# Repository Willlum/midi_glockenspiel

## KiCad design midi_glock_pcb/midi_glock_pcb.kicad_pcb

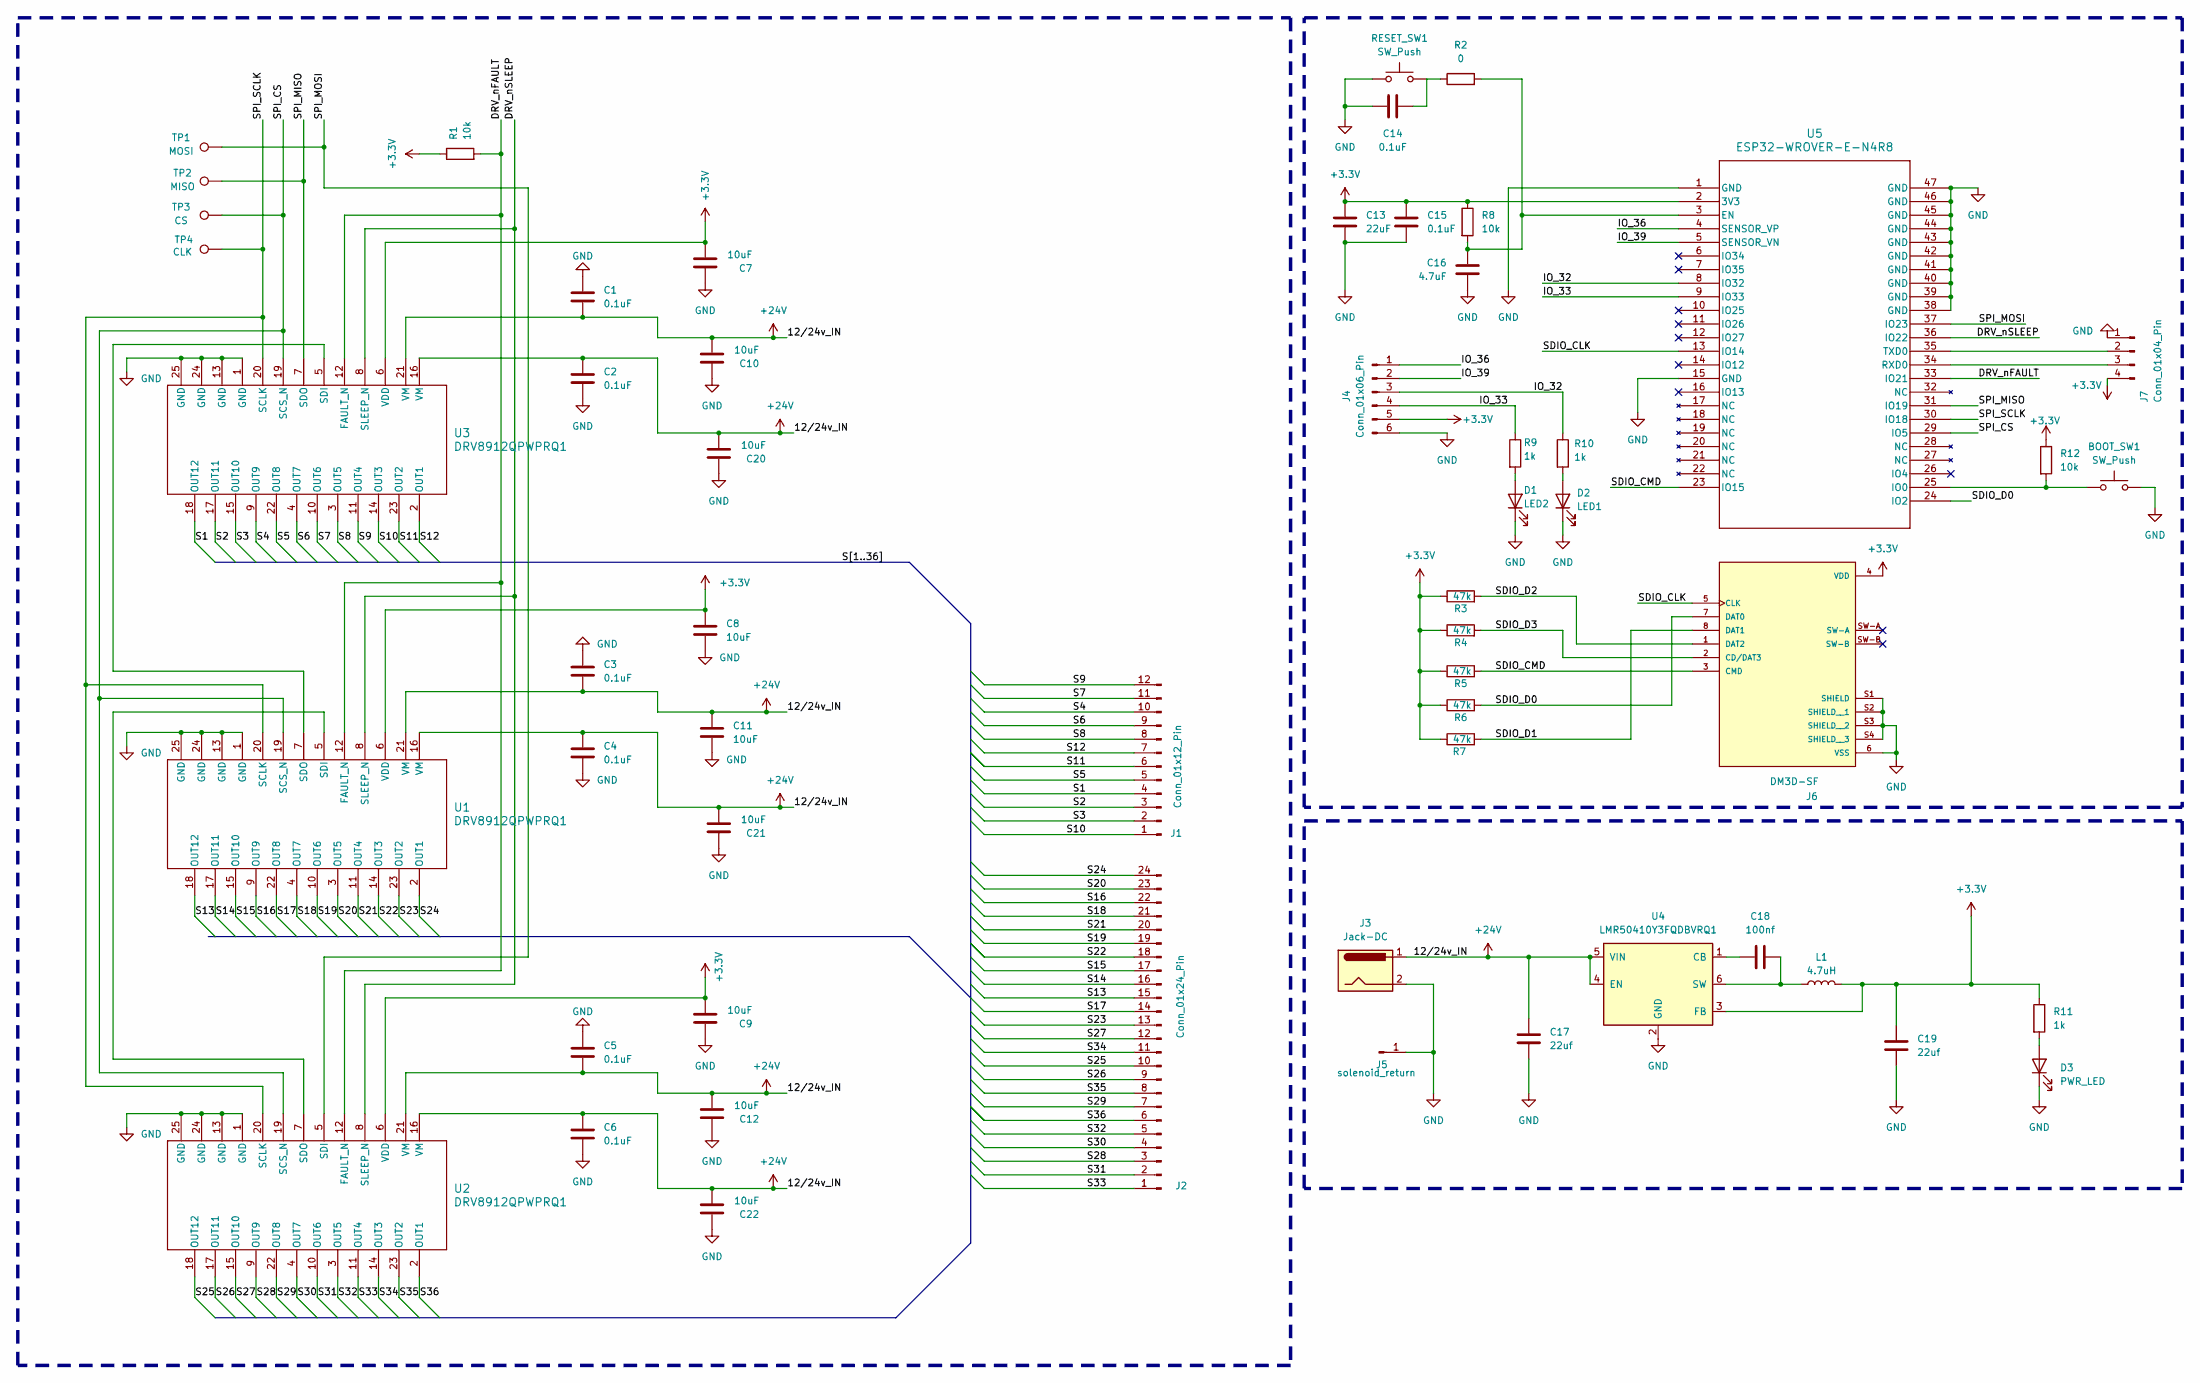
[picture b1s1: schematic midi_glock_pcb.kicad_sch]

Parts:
BOOT_SW1: SW_Push; SW_SPST_Omron_B3FS-100xP
C1, C2, C3, C4, C5, C6, C14, C15: 0.1uF; C_0603_1608Metric_Pad1.08x0.95mm_HandSolder
C7, C8, C9: 10uF; C_0805_2012Metric_Pad1.18x1.45mm_HandSolder
C10, C11, C12, C20, C21, C22: 10uF; C_1206_3216Metric
C13: 22uF; C_1210_3225Metric
C16: 4.7uF; C_0805_2012Metric_Pad1.18x1.45mm_HandSolder
C17, C19: 22uf; C_1210_3225Metric
C18: 100nf; C_0603_1608Metric_Pad1.08x0.95mm_HandSolder
D1: LED2; LED_0805_2012Metric_Pad1.15x1.40mm_HandSolder
D2: LED1; LED_0805_2012Metric_Pad1.15x1.40mm_HandSolder
D3: PWR_LED; LED_0805_2012Metric_Pad1.15x1.40mm_HandSolder
J1: Conn_01x12_Pin; PHOENIX_1989845
J2: Conn_01x24_Pin; PHOENIX_1990232
J3: Jack-DC; BarrelJack_Horizontal
J4: Conn_01x06_Pin; PinHeader_2x03_P2.54mm_Vertical
J5: solenoid_return; Pin_D1.3mm_L11.0mm_LooseFit
J6: DM3D-SF; HRS_DM3D-SF; PARTREV 2017.1
J7: Conn_01x04_Pin; PinHeader_1x04_P2.54mm_Vertical
L1: 4.7uH; IND_SRP4020TA-4R7M
R1, R8, R12: 10k; R_0603_1608Metric_Pad0.98x0.95mm_HandSolder
R2: 0; R_0603_1608Metric_Pad0.98x0.95mm_HandSolder
R3, R4, R5, R6, R7: 47k; R_0603_1608Metric_Pad0.98x0.95mm_HandSolder
R9, R10, R11: 1k; R_0603_1608Metric_Pad0.98x0.95mm_HandSolder
RESET_SW1: SW_Push; SW_SPST_Omron_B3FS-100xP
TP1: MOSI; TestPoint_Pad_D1.0mm
TP2: MISO; TestPoint_Pad_D1.0mm
TP3: CS; TestPoint_Pad_D1.0mm
TP4: CLK; TestPoint_Pad_D1.0mm
U1, U2, U3: DRV8912QPWPRQ1; PWP0024N_N
U4: LMR50410Y3FQDBVRQ1; SOT-23-6
U5: ESP32-WROVER-E-N4R8; ESP32­WROVER­E&slash_ESP32­WROVER­IE_EXP

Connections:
+3.3V: C7.2, C8.1, C9.2, C13.1, C15.1, C19.1, J4.5, J6.4 (VDD), J7.4, L1.2, R1.1, R3.1, R4.1, R5.1, R6.1, R7.1, R8.1, R11.1, R12.1, U1.6 (VDD), U2.6 (VDD), U3.6 (VDD), U4.3 (FB), U5.2 (3V3)
+24V: C1.2, C2.2, C3.2, C4.2, C5.2, C6.2, C10.2, C11.2, C12.2, C17.1, C20.2, C21.2, C22.2, J3.1, U1.16 (VM), U1.21 (VM), U2.16 (VM), U2.21 (VM), U3.16 (VM), U3.21 (VM), U4.4 (EN), U4.5 (VIN)
/DRV_nFAULT: R1.2, U1.12 (FAULT_N), U2.12 (FAULT_N), U3.12 (FAULT_N), U5.33 (IO21)
/DRV_nSLEEP: U1.8 (SLEEP_N), U2.8 (SLEEP_N), U3.8 (SLEEP_N), U5.36 (IO22)
/IO_32: J4.3, R10.1, U5.8 (IO32)
/IO_33: J4.4, R9.1, U5.9 (IO33)
/IO_36: J4.1, U5.4 (SENSOR_VP)
/IO_39: J4.2, U5.5 (SENSOR_VN)
/S1: J1.4, U3.18 (OUT12)
/S2: J1.3, U3.17 (OUT11)
/S3: J1.2, U3.15 (OUT10)
/S4: J1.10, U3.9 (OUT9)
/S5: J1.5, U3.22 (OUT8)
/S6: J1.9, U3.4 (OUT7)
/S7: J1.11, U3.10 (OUT6)
/S8: J1.8, U3.3 (OUT5)
/S9: J1.12, U3.11 (OUT4)
/S10: J1.1, U3.14 (OUT3)
/S11: J1.6, U3.23 (OUT2)
/S12: J1.7, U3.2 (OUT1)
/S13: J2.15, U1.18 (OUT12)
/S14: J2.16, U1.17 (OUT11)
/S15: J2.17, U1.15 (OUT10)
/S16: J2.22, U1.9 (OUT9)
/S17: J2.14, U1.22 (OUT8)
/S18: J2.21, U1.4 (OUT7)
/S19: J2.19, U1.10 (OUT6)
/S20: J2.23, U1.3 (OUT5)
/S21: J2.20, U1.11 (OUT4)
/S22: J2.18, U1.14 (OUT3)
/S23: J2.13, U1.23 (OUT2)
/S24: J2.24, U1.2 (OUT1)
/S25: J2.10, U2.18 (OUT12)
/S26: J2.9, U2.17 (OUT11)
/S27: J2.12, U2.15 (OUT10)
/S28: J2.3, U2.9 (OUT9)
/S29: J2.7, U2.22 (OUT8)
/S30: J2.4, U2.4 (OUT7)
/S31: J2.2, U2.10 (OUT6)
/S32: J2.5, U2.3 (OUT5)
/S33: J2.1, U2.11 (OUT4)
/S34: J2.11, U2.14 (OUT3)
/S35: J2.8, U2.23 (OUT2)
/S36: J2.6, U2.2 (OUT1)
/SDIO_CLK: J6.5 (CLK), U5.13 (IO14)
/SDIO_CMD: J6.3 (CMD), R5.2, U5.23 (IO15)
/SDIO_D0: J6.7 (DAT0), R6.2, U5.24 (IO2)
/SDIO_D1: J6.8 (DAT1), R7.2
/SDIO_D2: J6.1 (DAT2), R3.2
/SDIO_D3: J6.2 (CD/DAT3), R4.2
/SPI_CS: TP3.1 (1_1), U1.19 (SCS_N), U2.19 (SCS_N), U3.19 (SCS_N), U5.29 (IO5)
/SPI_MISO: TP2.1 (1_1), U3.7 (SDO), U5.31 (IO19)
/SPI_MOSI: TP1.1 (1_1), U2.5 (SDI), U5.37 (IO23)
/SPI_SCLK: TP4.1 (1_1), U1.20 (SCLK), U2.20 (SCLK), U3.20 (SCLK), U5.30 (IO18)
GND: BOOT_SW1.1, C1.1, C2.1, C3.1, C4.1, C5.1, C6.1, C7.1, C8.2, C9.1, C10.1, C11.1, C12.1, C13.2, C14.1, C15.2, C16.2, C17.2, C19.2, C20.1, C21.1, C22.1, D1.1 (K), D2.1 (K), D3.1 (K), J3.2, J4.6, J5.1 (Pin_1_1), J6.6 (VSS), J6.S1 (SHIELD), J6.S2 (SHIELD__1), J6.S3 (SHIELD__2), J6.S4 (SHIELD__3), J7.1, RESET_SW1.1, U1.1 (GND), U1.13 (GND), U1.24 (GND), U1.25 (GND), U2.1 (GND), U2.13 (GND), U2.24 (GND), U2.25 (GND), U3.1 (GND), U3.13 (GND), U3.24 (GND), U3.25 (GND), U4.2 (GND), U5.1 (GND), U5.15 (GND), U5.38 (GND), U5.39 (GND), U5.40 (GND), U5.41 (GND), U5.42 (GND), U5.43 (GND), U5.44 (GND), U5.45 (GND), U5.46 (GND), U5.47 (GND)
unnamed: C14.2, R2.1, RESET_SW1.2
unnamed: D1.2 (A), R9.2
unnamed: D2.2 (A), R10.2
unnamed: D3.2 (A), R11.2
unnamed: J7.2, U5.35 (TXD0)
unnamed: J7.3, U5.34 (RXD0)
unnamed: U1.5 (SDI), U2.7 (SDO)
unnamed: U1.7 (SDO), U3.5 (SDI)
unnamed: C18.1, U4.1 (CB)
unnamed: C18.2, L1.1, U4.6 (SW)
unnamed: C16.1, R2.2, R8.2, U5.3 (EN)
unnamed: BOOT_SW1.2, R12.2, U5.25 (IO0)

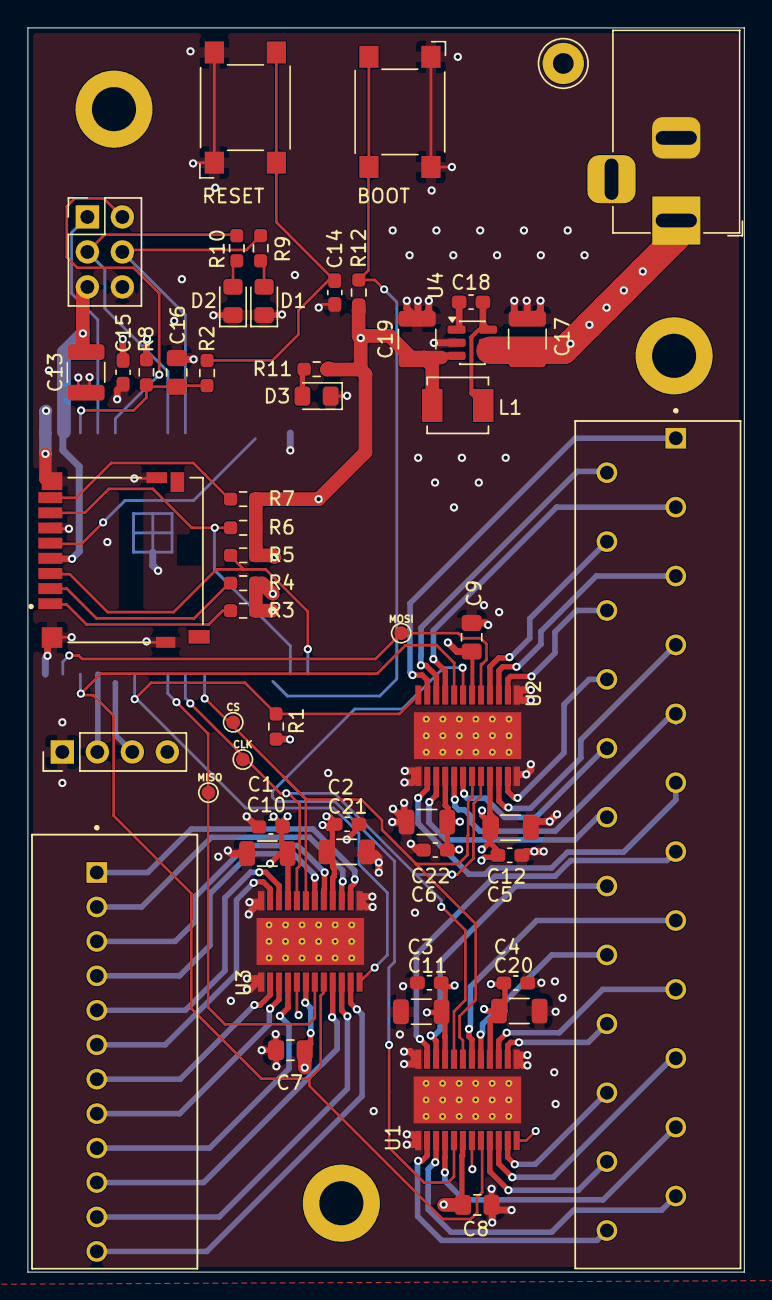
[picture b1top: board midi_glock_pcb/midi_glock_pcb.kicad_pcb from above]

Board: 4 copper layers, 52.0 x 90.3 mm, 56 parts (1 on the bottom side), 67 nets.

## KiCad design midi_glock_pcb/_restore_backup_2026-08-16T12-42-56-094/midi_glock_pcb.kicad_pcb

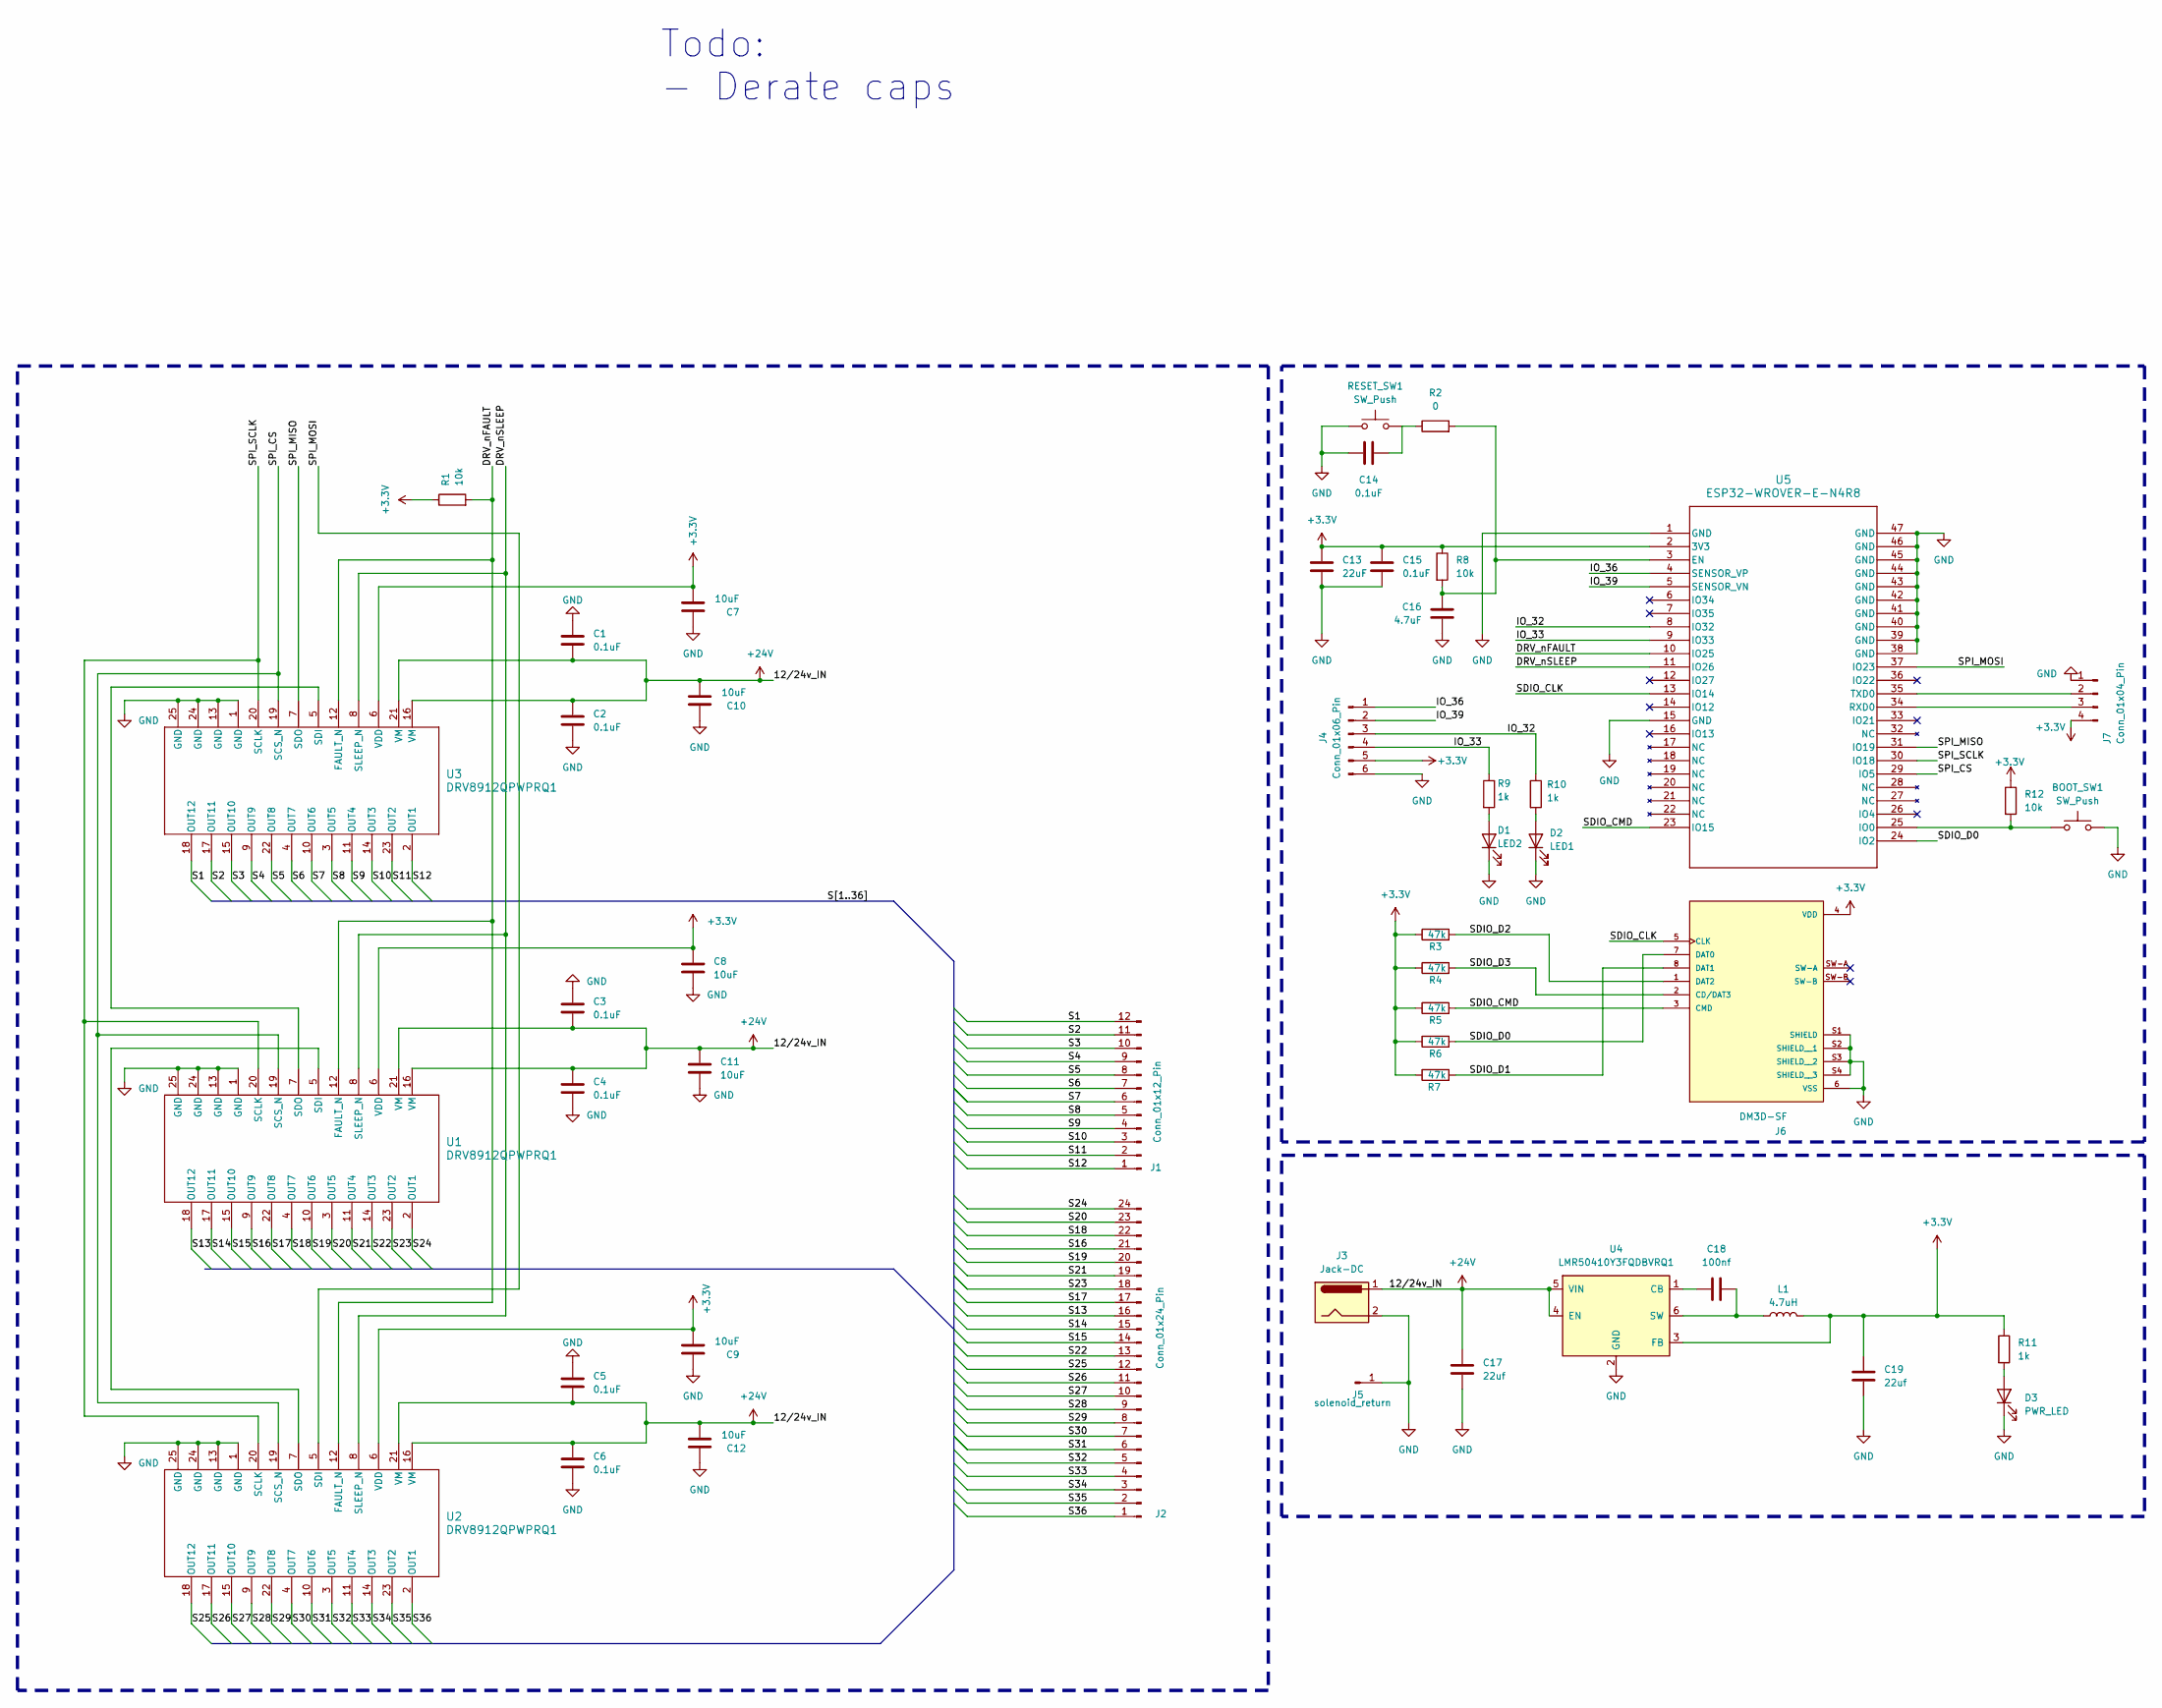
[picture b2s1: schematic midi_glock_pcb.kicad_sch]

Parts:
BOOT_SW1: SW_Push; SW_SPST_Omron_B3FS-100xP
C1, C2, C3, C4, C5, C6, C14, C15: 0.1uF; C_0805_2012Metric_Pad1.18x1.45mm_HandSolder
C7, C8, C9, C10, C11, C12: 10uF; C_0805_2012Metric_Pad1.18x1.45mm_HandSolder
C13: 22uF; C_0805_2012Metric_Pad1.18x1.45mm_HandSolder
C16: 4.7uF; C_0805_2012Metric_Pad1.18x1.45mm_HandSolder
C17, C19: 22uf; C_0805_2012Metric_Pad1.18x1.45mm_HandSolder
C18: 100nf; C_0805_2012Metric_Pad1.18x1.45mm_HandSolder
D1: LED2; LED_0805_2012Metric_Pad1.15x1.40mm_HandSolder
D2: LED1; LED_0805_2012Metric_Pad1.15x1.40mm_HandSolder
D3: PWR_LED; LED_0805_2012Metric_Pad1.15x1.40mm_HandSolder
J1: Conn_01x12_Pin; PHOENIX_1989845
J2: Conn_01x24_Pin; PHOENIX_1990232
J3: Jack-DC; BarrelJack_Horizontal
J4: Conn_01x06_Pin; PinHeader_2x03_P2.54mm_Vertical
J5: solenoid_return; Pin_D1.3mm_L11.0mm_LooseFit
J6: DM3D-SF; HRS_DM3D-SF; PARTREV 2017.1
J7: Conn_01x04_Pin; PinHeader_1x04_P2.54mm_Vertical
L1: 4.7uH; IND_SRP4020TA-4R7M
R1, R8, R12: 10k; R_0805_2012Metric_Pad1.20x1.40mm_HandSolder
R2: 0; R_0805_2012Metric_Pad1.20x1.40mm_HandSolder
R3, R4, R5, R6, R7: 47k; R_0805_2012Metric_Pad1.20x1.40mm_HandSolder
R9, R10, R11: 1k; R_0805_2012Metric_Pad1.20x1.40mm_HandSolder
RESET_SW1: SW_Push; SW_SPST_Omron_B3FS-100xP
U1, U2, U3: DRV8912QPWPRQ1; PWP0024N_N
U4: LMR50410Y3FQDBVRQ1; SOT-23-6
U5: ESP32-WROVER-E-N4R8; ESP32­WROVER­E&slash_ESP32­WROVER­IE_EXP

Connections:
+3.3V: C7.2, C8.1, C9.2, C13.1, C15.1, C19.1, J4.5, J6.4 (VDD), J7.4, L1.2, R1.1, R3.1, R4.1, R5.1, R6.1, R7.1, R8.1, R11.1, R12.1, U1.6 (VDD), U2.6 (VDD), U3.6 (VDD), U4.3 (FB), U5.2 (3V3)
+24V: C1.2, C2.2, C3.2, C4.2, C5.2, C6.2, C10.2, C11.2, C12.2, C17.1, J3.1, U1.16 (VM), U1.21 (VM), U2.16 (VM), U2.21 (VM), U3.16 (VM), U3.21 (VM), U4.4 (EN), U4.5 (VIN)
/DRV_nFAULT: R1.2, U1.12 (FAULT_N), U2.12 (FAULT_N), U3.12 (FAULT_N), U5.10 (IO25)
/DRV_nSLEEP: U1.8 (SLEEP_N), U2.8 (SLEEP_N), U3.8 (SLEEP_N), U5.11 (IO26)
/IO_32: J4.3, R10.1, U5.8 (IO32)
/IO_33: J4.4, R9.1, U5.9 (IO33)
/IO_36: J4.1, U5.4 (SENSOR_VP)
/IO_39: J4.2, U5.5 (SENSOR_VN)
/S1: J1.12, U3.18 (OUT12)
/S2: J1.11, U3.17 (OUT11)
/S3: J1.10, U3.15 (OUT10)
/S4: J1.9, U3.9 (OUT9)
/S5: J1.8, U3.22 (OUT8)
/S6: J1.7, U3.4 (OUT7)
/S7: J1.6, U3.10 (OUT6)
/S8: J1.5, U3.3 (OUT5)
/S9: J1.4, U3.11 (OUT4)
/S10: J1.3, U3.14 (OUT3)
/S11: J1.2, U3.23 (OUT2)
/S12: J1.1, U3.2 (OUT1)
/S13: J2.16, U1.18 (OUT12)
/S14: J2.15, U1.17 (OUT11)
/S15: J2.14, U1.15 (OUT10)
/S16: J2.21, U1.9 (OUT9)
/S17: J2.17, U1.22 (OUT8)
/S18: J2.22, U1.4 (OUT7)
/S19: J2.20, U1.10 (OUT6)
/S20: J2.23, U1.3 (OUT5)
/S21: J2.19, U1.11 (OUT4)
/S22: J2.13, U1.14 (OUT3)
/S23: J2.18, U1.23 (OUT2)
/S24: J2.24, U1.2 (OUT1)
/S25: J2.12, U2.18 (OUT12)
/S26: J2.11, U2.17 (OUT11)
/S27: J2.10, U2.15 (OUT10)
/S28: J2.9, U2.9 (OUT9)
/S29: J2.8, U2.22 (OUT8)
/S30: J2.7, U2.4 (OUT7)
/S31: J2.6, U2.10 (OUT6)
/S32: J2.5, U2.3 (OUT5)
/S33: J2.4, U2.11 (OUT4)
/S34: J2.3, U2.14 (OUT3)
/S35: J2.2, U2.23 (OUT2)
/S36: J2.1, U2.2 (OUT1)
/SDIO_CLK: J6.5 (CLK), U5.13 (IO14)
/SDIO_CMD: J6.3 (CMD), R5.2, U5.23 (IO15)
/SDIO_D0: J6.7 (DAT0), R6.2, U5.24 (IO2)
/SDIO_D1: J6.8 (DAT1), R7.2
/SDIO_D2: J6.1 (DAT2), R3.2
/SDIO_D3: J6.2 (CD/DAT3), R4.2
/SPI_CS: U1.19 (SCS_N), U2.19 (SCS_N), U3.19 (SCS_N), U5.29 (IO5)
/SPI_MISO: U3.7 (SDO), U5.31 (IO19)
/SPI_MOSI: U2.5 (SDI), U5.37 (IO23)
/SPI_SCLK: U1.20 (SCLK), U2.20 (SCLK), U3.20 (SCLK), U5.30 (IO18)
GND: BOOT_SW1.1, C1.1, C2.1, C3.1, C4.1, C5.1, C6.1, C7.1, C8.2, C9.1, C10.1, C11.1, C12.1, C13.2, C14.1, C15.2, C16.2, C17.2, C19.2, D1.1 (K), D2.1 (K), D3.1 (K), J3.2, J4.6, J5.1 (Pin_1_1), J6.6 (VSS), J6.S1 (SHIELD), J6.S2 (SHIELD__1), J6.S3 (SHIELD__2), J6.S4 (SHIELD__3), J7.1, RESET_SW1.1, U1.1 (GND), U1.13 (GND), U1.24 (GND), U1.25 (GND), U2.1 (GND), U2.13 (GND), U2.24 (GND), U2.25 (GND), U3.1 (GND), U3.13 (GND), U3.24 (GND), U3.25 (GND), U4.2 (GND), U5.1 (GND), U5.15 (GND), U5.38 (GND), U5.39 (GND), U5.40 (GND), U5.41 (GND), U5.42 (GND), U5.43 (GND), U5.44 (GND), U5.45 (GND), U5.46 (GND), U5.47 (GND)
unnamed: C14.2, R2.1, RESET_SW1.2
unnamed: D1.2 (A), R9.2
unnamed: D2.2 (A), R10.2
unnamed: D3.2 (A), R11.2
unnamed: J7.2, U5.35 (TXD0)
unnamed: J7.3, U5.34 (RXD0)
unnamed: U1.5 (SDI), U2.7 (SDO)
unnamed: U1.7 (SDO), U3.5 (SDI)
unnamed: C18.1, U4.1 (CB)
unnamed: C18.2, L1.1, U4.6 (SW)
unnamed: C16.1, R2.2, R8.2, U5.3 (EN)
unnamed: BOOT_SW1.2, R12.2, U5.25 (IO0)

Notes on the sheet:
Todo: - Derate caps

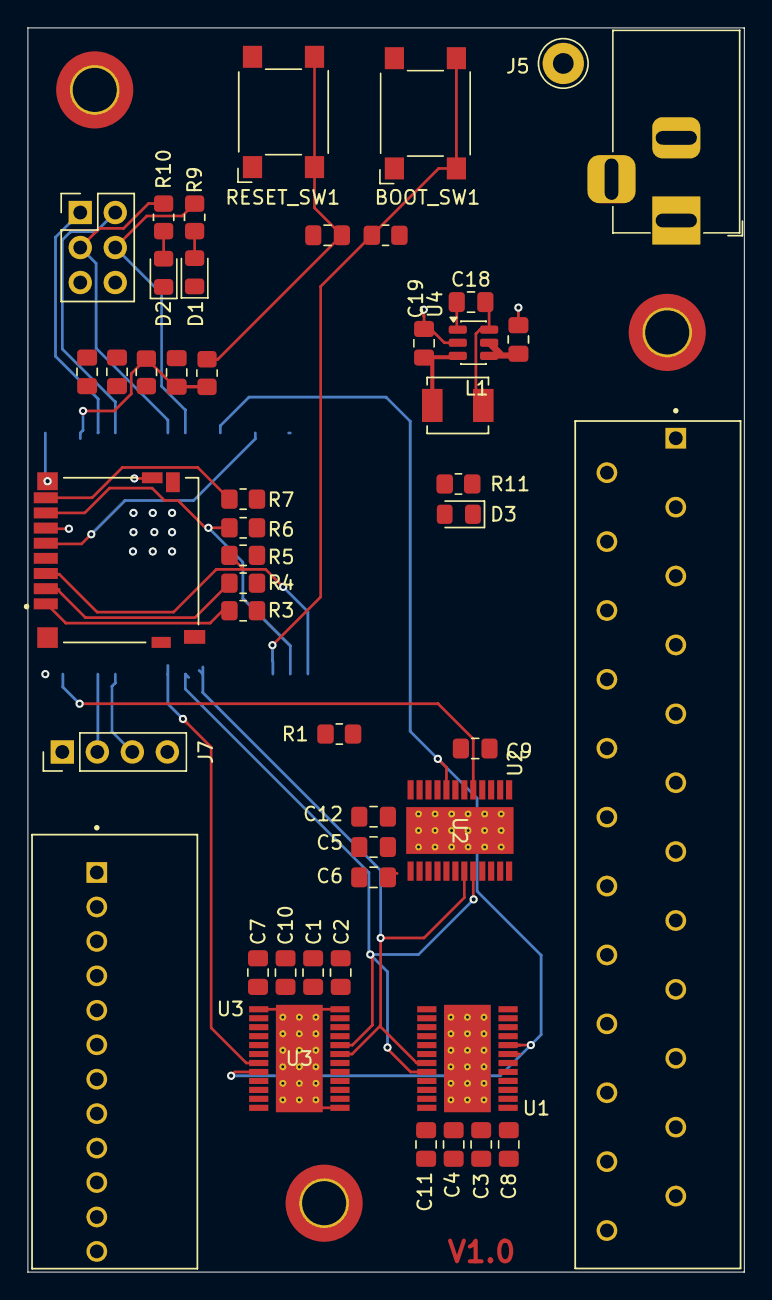
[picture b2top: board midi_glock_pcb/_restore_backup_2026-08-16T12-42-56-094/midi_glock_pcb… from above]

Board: 4 copper layers, 52.0 x 90.3 mm, 49 parts (1 on the bottom side), 67 nets.

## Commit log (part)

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2026-03-25 init
2026-03-25 formatting
